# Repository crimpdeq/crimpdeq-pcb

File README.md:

# Crimpdeq PCB

PCB design for Crimpdeq in [tscircuit](https://tscircuit.com), source in
[`index.circuit.tsx`](index.circuit.tsx). See the [Crimpdeq book](https://book.crimpdeq.com/)
for assembly, flashing, and calibration.

V4 started as a tscircuit port of [v2.0.0](https://github.com/crimpdeq/crimpdeq-pcb/tree/v2.0.0)
with the HX711 replaced by a TI ADS1220 24-bit ADC, developed in
[crimpdeq-tscircuit](https://github.com/crimpdeq/crimpdeq-tscircuit) (history merged here).
The KiCad revisions V1 to V3 remain available at their release tags.

## Revisions

Use the [firmware](https://github.com/crimpdeq/crimpdeq-firmware) and
[case](https://github.com/crimpdeq/crimpdeq-case) releases in the row for your PCB revision.
From V2 on, the PCB, firmware, and case share the major version; V1 uses firmware and case
`v0.4.0`.

| PCB revision | PCB release | Source | ADC | Firmware | Case |
| --- | --- | --- | --- | --- | --- |
| V4 (in development) | not released | tscircuit | ADS1220 | not released | not released |
| V3 | [`v3.0.0`](https://github.com/crimpdeq/crimpdeq-pcb/releases/tag/v3.0.0) | KiCad | ADS1220 | [`v3.0.0`](https://github.com/crimpdeq/crimpdeq-firmware/releases/tag/v3.0.0) | [`v3.1.0`](https://github.com/crimpdeq/crimpdeq-case/releases/tag/v3.1.0) |
| V2 | [`v2.0.0`](https://github.com/crimpdeq/crimpdeq-pcb/releases/tag/v2.0.0) | KiCad | HX711 | [`v2.1.0`](https://github.com/crimpdeq/crimpdeq-firmware/releases/tag/v2.1.0) | [`v2.0.0`](https://github.com/crimpdeq/crimpdeq-case/releases/tag/v2.0.0) |
| V1 | [`v1.0.1`](https://github.com/crimpdeq/crimpdeq-pcb/releases/tag/v1.0.1) | KiCad | HX711 | [`v0.4.0`](https://github.com/crimpdeq/crimpdeq-firmware/releases/tag/v0.4.0) | [`v0.4.0`](https://github.com/crimpdeq/crimpdeq-case/releases/tag/v0.4.0) |

V3 firmware and case do not work with V4: V4 is 17 × 25.75 mm with the ESP32-C3 antenna
overhanging its edge, its wire pads differ, its load cell is powered only while
firmware sets the ADS1220 `PSW` bit (see below), and its status LED takes data on IO20
and is powered only while IO2 is low.

## Board

- Board: 17 × 25.75 mm, 4 layers, components on both sides (v2.0.0: 23 × 63.8 mm, 2 layers)
- Top: ESP32-C3-MINI-1 (its antenna overhangs the board edge: no board under it),
  USB-C (TYPE-C-31-M-12, flush with the opposite edge), USB ESD, both LEDs, load cell
  ferrites (FB1, FB2)
- Bottom: charger, power path, 3V3 buck, MAX17048, ADS1220 and passives
- Stackup: GND pour on every layer; inner2 (next to the bottom side) is a solid GND
  plane under the buck, the ADS1220 front end and the USB pair's inner1 run, and inner1
  under its top-side run (`lib/gndPlane.ts`); signals run on the other layers and the
  rest of the inner layers. GND stitching vias at the module EPAD, the ADS1220 bypass
  capacitors and AVSS, the buck, the USB pair's vias and the board edges
- Design rules (PCBWay): 5/5 mil track/space, vias 0.3 mm drill / 0.5 mm pad,
  0.3 mm copper-to-edge

## ADS1220 hookup

| ADS1220 | Net |
| --- | --- |
| AVDD, DVDD | 3V3 |
| REFP0 | load cell E+: 3V3 through 10 Ω (R22), 1 µF to GND (C14) |
| REFN0, AIN3/REFN1 | load cell E−, switched to AVSS by the internal low-side switch |
| AVSS, DGND, CLK, EP | GND |
| SCLK / DIN / DOUT/DRDY / CS | GPIO5 / GPIO4 / GPIO1 / GPIO3, CS pulled up to 3V3 (100 kΩ) |
| DRDY | GPIO0 |
| AIN0 / AIN1 | load cell S+ / S− through a GHz ferrite (FB1/FB2, at J3) and 1 kΩ each, 10 nF C0G differential (~8 kHz), 22 pF and 1 nF C0G to GND each |
| AIN2 | not connected |

The bridge is powered only while the low-side switch is closed: firmware must set
`PSW = 1` (config register 2), which closes the switch on START/SYNC and opens it on
POWERDOWN. REFP0 and REFN0 sense the bridge on both sides, so the reference stays
ratiometric across R22 and the switch.

Wire pads: J3 `E+ S+ S- E-` (E+ = filtered 3V3, E− = low-side switch), J4 `SW- SW+ B+ B-` (SW+ = B+, SW− = power-path input).
v2.0.0 names these the other way round: its `SW+` pad is the power-path input and `VBAT` is the battery.
J3's labels are on the bottom side only: FB1/FB2 sit next to its pads on the top side.

The board ends where U1's antenna starts, so the antenna overhangs the board by 5.4 mm.
Espressif recommends placing the PCB antenna outside the base board and cutting off any
board under it. U1's top pads end 0.3 mm from the edge (PCBWay's minimum). Coordinates
keep the origin of the earlier 31.5 mm board, whose top edge was at the antenna tip, so
the board center is at y = −2.875 mm. The case must hold the overhanging antenna
without touching it.

## Changes vs v2.0.0 beyond the ADC

- HX711 support parts (Q1, R5, R6, C11 VBG) removed; ADS1220 decoupling added.
- Load cell excitation switched off in power-down by the ADS1220 low-side switch
  (v2.0.0 turns the HX711 E+ regulator off instead).
- Smaller, equivalent parts: L1 FTC252012S2R2MBCA (2520, 2.2 µH, 3 A), D2/D8 B5819WS (SOD-323).
- RGB LED: XL-2121RGBC-2812B (2 × 2 mm, WS2812 protocol). Its datasheet gives
  3.0–5.5 V only as the supply limit and full function at 4.5–5.5 V, so at 3.3 V
  blue and green may be dim; the WS2812B-5050 (3.7–5.3 V) was also run at 3.3 V.
- Added: 4.7 kΩ I2C pull-ups (MAX17048), 100 nF at the RGB LED, a battery GND pad (B−).
- ADS1220 100 nF bypass capacitors (C11, C13) 0.5 mm from AVDD/DVDD, with GND vias at
  their GND pads; 3V3 reaches their pads before the pins (from the 3V3 trunk through C13).
- RGB LED supply switched by a P-MOSFET (Q3, NTK3139P), so deep sleep doesn't pay
  its idle current (V3 fed it from 3V3 whenever the battery switch was on,
  [crimpdeq-pcb#30](https://github.com/crimpdeq/crimpdeq-pcb/issues/30)): IO2 low
  powers D4, and the 100 kΩ gate pull-up (R26) keeps it off in deep sleep and reset
  and gives the IO2 strapping pin the pull-up Espressif recommends. The LED data moved
  to IO20 (RXD0, through R13). Firmware must keep the data line low while D4 is off:
  driven high, it can power D4 through the LED's input. Q3's 3V3 side doesn't run
  along the ADS1220 supply path (`scripts/drc.ts` checks this).
- USB-C shield tied directly to GND (R17 0 Ω removed).
- 3V3 buck laid out after the SY8088 layout notes, with its power copper routed by hand:
  C15's GND pad lines up with the gap between FB and IN, so a 0.8 mm strap reaches
  the GND pin under the package; C17's GND pad joins C15's; LX reaches L1 in 0.7 mm;
  the feedback divider sits at the FB pin and senses 3V3 at C17.
- 3V3 from C17 to the ESP32 decoupling (D3, C4, C2, C1, C9) is a 0.4 mm hand-routed
  trunk (v2.0.0 used up to 0.61 mm).
- ESD diode and receptacle GND pads are tied by hand to the J2 GND pins, the shell legs
  and (D7) a via.
- USB D-/D+ run as a pair (0.15 mm at 0.3 mm pitch) from the ESD diodes to IO18/IO19:
  on inner1 over a solid inner2 GND region, then through a via pair below U1 and on the
  top side over a solid inner1 region. The lengths differ by 0.3 mm; `scripts/drc.ts`
  (`usbPair`) checks that both run on the same layers within 0.5 mm. No impedance
  control is ordered: at USB full speed (12 Mbit/s) these 16 mm are electrically short.
- Download-mode recovery: bottom-side pads under U1, EN (TP1), GND (TP2) and BOOT
  (TP3, IO9), 1.5 mm apart. Hold BOOT to GND and tap EN to GND (tweezers bridge
  neighbouring pads). With the battery switch off, plugging USB in is a power-on
  reset, so holding BOOT while plugging in does the same. A 10 kΩ pull-up (R25)
  holds IO8 high, which download mode needs.
- RF filtering of the load cell inputs against BLE TX pickup
  ([crimpdeq-tscircuit#23](https://github.com/crimpdeq/crimpdeq-tscircuit/issues/23)): on the KiCad
  revision-3 board, BLE transmissions add spikes of up to 0.98 kg that enter at AIN0/AIN1.
  Each input has, between its 1 kΩ resistor and the pin, 22 pF C0G to GND (self-resonant
  near 2.4 GHz; C20, C21) and 1 nF C0G common-mode to GND (C22, C23, a tenth of C12),
  and S+/S− have GHz ferrites (BLM15HG102SN1D, FB1, FB2) at J3. Vias can't go under
  U1's left pad column, so AIN0's capacitors return to C11's GND via and AIN1's to U1's
  GND20 pad (C21, through a via) and C3's GND pad (C23). S+/S− run side by side on
  inner1, 0.35 mm apart from beside U3 down to the ferrites.
- The buck EN pull-up (R14) gets VSYS from U6.IN over inner1: on the bottom side the GND
  strap, U6 and L1 close U6.IN off from the feedback divider column.
- All copper is fixed (see Routing): hand-written traces for the buck, the 3V3 trunk,
  the USB and ESD fan-out, the charger signals, U5's I2C and alert, the ADS1220 fan-out,
  front end and supply, the load cell lines and the RGB LED corner; generated routes
  for the other nets.

## Verify

```sh
bun install --frozen-lockfile   # exact tool versions from bun.lock
npm run verify   # netlist + routing baselines, placement, schematic, build, per-check DRC,
                 # gerber shorts, fab paste and copper
npm run fab      # PCBWay package in dist/fab/
```

`scripts/drc.ts` runs every PCB check individually because the built-in DRC
aborts when its copper-pour check crashes, and adds minimum trace width, inner-layer
GND plane, 3V3 supply topology (at most 3 mm of the buck -> U1 3V3 path below
0.25 mm), USB pair and through-via checks. The board sets `isViaInPadAllowed` for C13's 3V3 via,
the only via whose drill overlaps a pad (there is no room for it between C13's pads);
`scripts/drc.ts` runs `checkViasInPads` without that flag and fails any other via in
a pad.
`scripts/netlist.py` and `scripts/routing.py` compare
connectivity and routed copper against `scripts/netlist.expected.json` and
`scripts/routing.expected.json`.

`scripts/fab-json.ts` fixes the paste and GND pours in the copy of `circuit.json`
that `npm run fab` exports, and checks the result: tscircuit leaves pill and
polygon pads without paste, shrinks all paste to 49 % of the pad area, pastes
every plated hole on both sides, and leaves floating pour copper. It also
unrotates the pads at multiples of 90° (size swapped): tscircuit flashes rounded
rotated pads with a `%LR` load rotation that some CAM tools ignore, and `npm run fab`
fails if any `%LR` is left.

Every via is a through via: the board is ordered as a standard 4-layer stackup.
tscircuit core gives vias in fixed traces (non-empty `pcbPath`) only the layers they
join, which exports blind/buried drill files with GND pour over their drill on the
other layers; `scripts/patch-core.mjs` (run on install) gives them all layers, as
core already does for autorouted vias. `scripts/drc.ts` (`throughVias`) fails on
any via that doesn't span all layers, and `npm run fab` fails on any drill file
besides `drill-PTH.drl` and `drill-NPTH.drl`.

`npm run fab` also joins each slot (J2's shell legs) onto one `X..Y..G85X..Y..`
line: the exporter puts the start hit and `G85` on separate lines, which GerbView
reads as one route through the following holes, and `npm run fab` fails if a `G85`
line is left without its start. The zip leaves out `F_Fab.gbr` and `B_Fab.gbr`
(assembly outlines, which the assembly drawings carry).

## Online viewer

<https://tscircuit.crimpdeq.com> serves the PCB, schematic and 3D viewer as a
static site on Cloudflare Pages (project `crimpdeq-tscircuit`).
`.github/workflows/site.yml` rebuilds and deploys it on every push to `main`
(repository secret `CLOUDFLARE_API_TOKEN`, Cloudflare Pages: Edit). Both the
workflow and `npm run site` refuse to publish a routing that differs from
`scripts/routing.expected.json`.

```sh
npm run site          # static site in dist/site/
npm run site:deploy   # build and upload it (needs `npx wrangler login`)
```

## PCBWay order

`dist/fab/` contains `pcbway_gerbers.zip` (Gerbers + drills), `pcbway_bom.csv`
(grouped by manufacturer part number, with LCSC codes as sourcing hints and
substitution notes), `pcbway_centroid.csv` (mm, in the Gerbers' coordinates, whose origin is
2.875 mm above the board center) and
top/bottom assembly drawings from `scripts/assembly.ts` (bottom mirrored, as seen
from below; the corner triangle marks pin 1, or the cathode of diodes and LEDs).

The silkscreen has no reference designators, which are illegible at this size and
are on the assembly drawings: its only text is the J3/J4 wire pad labels and the
EN/GND/BOOT recovery pad labels, as large as the pads and parts around them allow
and running along their pad columns. `npm run fab` widens every silkscreen line
below 0.15 mm (text is stroked at 9 % of its font size) to 0.15 mm, PCBWay's minimum. The polarized diodes (D1, D2, D8) have their
silkscreen outline closed at the cathode; D3, D7, D9 and D10 are bidirectional.

`.github/workflows/release.yml` builds the same package on every published GitHub
release, after `npm run verify` passes, and attaches it to the release as
`crimpdeq-pcb-<tag>-*` with a `SHA256SUMS` file. Pull requests that change
the fab scripts and manual runs only build it, as a workflow artifact.

Quote settings: 4 layers, 17 × 25.75 mm, 1.6 mm FR-4, min track/spacing 5/5 mil,
min hole 0.3 mm, assembly on both sides. The centroid rotations come from
tscircuit; ask PCBWay to confirm orientation against the assembly drawings.

Assembly notes for PCBWay:

- Reflow the bottom side first; the top carries the heavy parts (U1, J2).
- J2's four shell legs are pin-in-paste in the top reflow: top paste over the leg
  pads, none on the bottom.
- The J3/J4 wire pads have no paste; the load cell and battery wires are
  hand-soldered afterwards.
- Paste is 1:1 on normal pads and 50–60 % on the thermal pads (U1 EPAD, U3 and
  U5 exposed pads).

## Routing

All copper is fixed; the autorouter has nothing left to route.

- GND is left to the GND pours on all four layers and the stitching vias.
  `lib/gndPlaneRouter.ts` removes it from the autorouter input, and
  `checkEachPcbPortConnectedToPcbTraces` fails if any GND pad ends up on its own
  copper island (a pad boxed in by other traces needs a via or a trace of its own,
  as C14's and U1.GND4's do).
- Traces with a layout intent are written by hand in `index.circuit.tsx` (see the
  design changes above).
- The other nets (VSYS, VBUS, VBAT, the rest of 3V3, the SPI clock and data, CS,
  the LED supply, switch gate and data, CHIP_PU, BOOT) are generated into
  `lib/handRoutes.ts` by `scripts/handroute.sh`. It builds the board without them
  and without the autorouter (`GND_ROUTER_SKIP=1`), then `scripts/handroute.ts`
  routes the nets in `scripts/handroute.json`, in that order, on a 0.05 mm grid over
  the four layers:
  0.127 mm to other nets, vias 0.15 mm from pads, through vias that block every
  layer, and the GND plane regions kept clear.

After a change to placement, footprints or the hand-written traces:

```sh
scripts/handroute.sh             # regenerates lib/handRoutes.ts
npm run verify                   # fails on the routing baseline: expected
python3 scripts/routing.py --update && npm run verify
```

If a net doesn't route, `scripts/handroute.sh` fails and leaves `lib/handRoutes.ts`
unchanged: move it earlier in `scripts/handroute.json` (earlier nets get the room) or
change the hand-written traces around it.

Hand-written traces are `<trace>` elements with a non-empty `pcbPath`
(`pcbPath={[toPort]}` for a straight line between pad centers): core fixes only
those, and the autorouter routed across `pcbPath={[]}` ones. `pcbStraightLine` ends
traces at the pad edge, and tscircuit then attaches the end to whichever pad covers
that point on any layer (here U1's pads on the top side). Core limits traces to a
power-to-ground capacitor to 1 mm and skips autorouting (and fails the build) if a
fixed trace is longer; capacitors with longer fixed traces set
`maxDecouplingTraceLength`.

The tscircuit autorouter is deterministic, but at this density it left via-to-pad
violations and shorts that its own DRC misses, routed across fixed traces, and placed
vias it checked on only some of the layers they cross. `scripts/search.py` (nudges
passives until the board routes clean) and its output depending on the platform
(macOS arm64 against Linux x64) only matter again if nets are left to it.
`lib/gndPlaneRouter.ts` keeps it in place: the stock solver with GND removed and the
`unbroken` inner-layer GND pours detached from GND, so they only keep other nets out.
Attached, the router escaped nearby GND pads into the pour with vias whose clearance
it checked only between the pad and pour layers; built as through vias, they landed
on pads on the other side (L1, C16, C17, C11, C12). Routing on only three layers (all
of inner2 reserved) left the board unroutable.

## Prompting AI agents

Agents follow `AGENTS.md` and the vendored tscircuit skill. tscircuit's
[prompting guide](https://docs.tscircuit.com/guides/circuit-generation/generating-circuit-boards-with-ai)
is written for new boards; a prompt for a change to this one should state:

- Goal: the change and why.
- Scope: the parts, nets or board area, by reference designator or net name.
- Parts: the manufacturer part number of new or changed parts.
- Side effects: whether placement, routed copper or connectivity may change, and whether
  to regenerate `dist/fab/`.
- Done: `npm run verify` passes, plus anything to inspect (PCB image, DRC result).

```text
<Change> because <reason>.
Affected: <reference designators, nets or board area>.
New parts: <manufacturer part number> (LCSC <code> as a sourcing hint).
May change: <placement | hand-written traces | generated routes | netlist | dist/fab/>.
Keep fixed: <parts or traces that must not move or reroute>.
Done when npm run verify passes; show the netlist and routing diffs before
updating their baselines.
```

The PCB was sponsored by [PCBWay](https://www.pcbway.com/), thank you! Working with them was incredibly easy and fast, and the resulting boards are high quality.

## License

This repository is source-available for personal and educational use only.

Commercial manufacture, sale of PCBs, sale of 3D-printed cases, kits, or assembled Crimpdeq devices requires prior written permission.

The vendored tscircuit skill in `.agents/skills/tscircuit/` keeps its own MIT license.

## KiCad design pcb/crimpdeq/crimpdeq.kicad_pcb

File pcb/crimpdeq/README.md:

# Crimpdeq — 30 x 30 mm Four-Layer Design

This is the repository's single canonical PCB design, released as PCB V3 in `v3.0.0`. It
includes corrected ESP32 module grounding, an ADS1220 load-cell front-end, and compact
power/USB routing.

- Board/project/rules/schematic: `crimpdeq.{kicad_pcb,kicad_pro,kicad_dru,kicad_sch}`
- Outline: 30.00 x 30.00 mm (30.05 x 30.05 mm including edge stroke)
- Components: 59 total, 38 front / 21 back
- U1 antenna and D4 LED: back; J2 USB-C and U3 ADS1220: front
- U1 pins 37–53, including EPAD 49, are connected to GND as required by Espressif.
- R20/R21/R22 provide 10 kΩ pull-ups for SDA, SCL, and the MAX17048 alert output.
- U3 ADS1220 (TSSOP-16, LCSC C48263) uses ratiometric +3V3 excitation (E+/REFP0) with
  E-/REFN0 on GND. AVDD/DVDD decoupling is C11 + C19. R7/R8 and 100 nF C0G C12 filter into AIN0/AIN1.
- SPI map: GPIO5 SCK, GPIO4 MOSI, GPIO3 CS, GPIO1 MISO (DOUT/~DRDY). R23–R26 are
  source-local 47 Ω series dampers on those four signals. CLK is grounded and dedicated DRDY is NC.
- The buck input, switch, output, and feedback components form a compact front-side cluster.
- Twelve dedicated GND stitching vias tie the outer floods to the solid L2 plane.
- All four load-cell pads (`E-`, `A-`, `A+`, `E+`) are together on the bottom edge near U3 and
  away from the antenna. `B-`, `B+`, `SW+`, and `SW-` are on the right edge, next to the USB-C
  connector.
- The ESP32 antenna body overhangs the top edge; its all-layer copper keepout is retained.
- The USB-C housing overhangs the bottom edge by 1.00 mm; connector copper remains in-board.
- L2 is a signal-free GND plane. L3 carries the 3V3 pour and low-speed signals.
- KiCad error-level DRC: zero violations and zero unconnected items.
- Schematic ERC and PCB/schematic parity: zero errors.

Production files:

- Gerbers, drills, BOM, and pick-and-place files: GitHub Release artifacts
- Assembly source and generators: `assembly/`

Check the manufacturer's DFM review on every order.

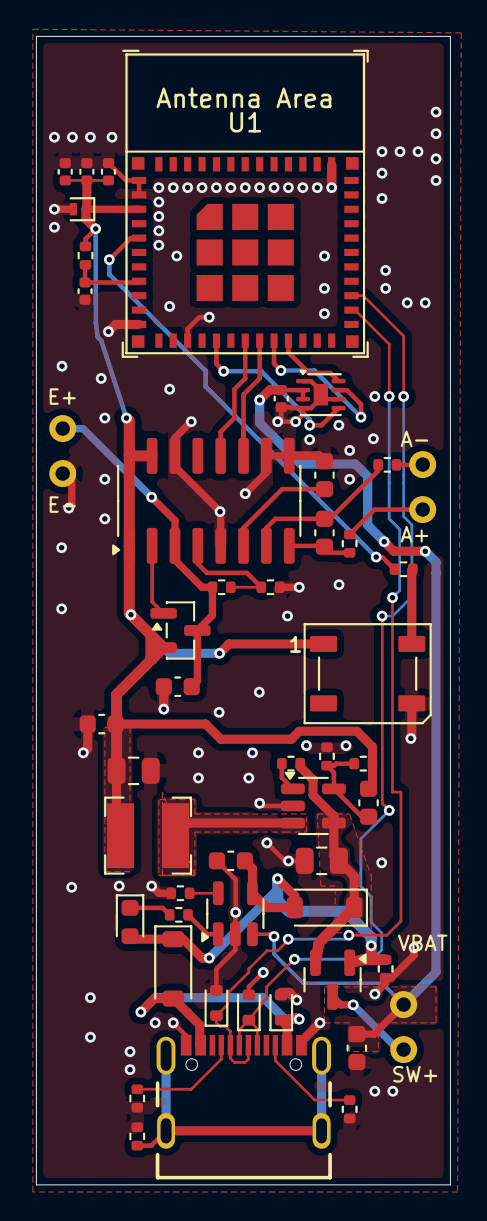
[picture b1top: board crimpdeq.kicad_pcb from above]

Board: 2 copper layers, 23.0 x 63.8 mm, 48 parts (0 on the bottom side), 34 nets.

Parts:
C1, C3: 1uF 16V; C_0402_1005Metric
C2, C18: 100nF 10V; C_0402_1005Metric
C4: 10nF 10V; C_0402_1005Metric
C5, C6: 4.7uF 16V; C_0603_1608Metric
C9, C10: 10uF; C_0603_1608Metric
C11, C12: 0.1uF; C_0603_1608Metric
C15, C17: 10uF 16V; C_0805_2012Metric
C16: 22pF 50V; C_0603_1608Metric
D1: LED; LED_0603_1608Metric
D2, D8: B5819W; D_SOD-123
D3: LESD8D3.3CAT5G; D_SOD-882
D4: WS2812B; LED_WS2812B_PLCC4_5.0x5.0mm_P3.2mm
D7, D9, D10: LESD5D5.0CT1G; D_SOD-523
J2: USB4105-GF-A; GCT_USB4105-GF-A
J3: Loadcell_Pads; External_Cable_Pads_Left
J4: Power_Sense_Pads; External_Cable_Pads_Right
L1: SPH4018H2R2MT (2.2uH 2.2A); L_Bourns-SRN4018
Q1: SS8550; SOT-23
Q2: DMG3415U; SOT-23
R1, R2, R14: 10kR 1%; R_0402_1005Metric
R3: 1kR 1%; R_0402_1005Metric
R5: 12kR 1%; R_0402_1005Metric
R6: 8k2R 1%; R_0402_1005Metric
R7, R8: 100R 1%; R_0402_1005Metric
R9, R15: 100kR 1%; R_0402_1005Metric
R13, R17: 0R 1%; R_0402_1005Metric
R16: 22k1R 1%; R_0402_1005Metric
R18, R19: 5k1R 1%; R_0402_1005Metric
U1: ESP32-C3-MINI-1
U2: MCP73831T-2ACI/OT; SOT-23-5
U3: HX711; SOP-16_3.9x9.9mm_P1.27mm
U5: MAX17048G+T10; TDFN-8-1EP_2x2mm_P0.5mm_EP0.8x1.2mm
U6: SY8088; SOT-23-5

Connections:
+3V3: C1.1, C2.1, C4.1, C9.1, C16.1, C17.1, D3.1 (A1), D4.1 (VDD), L1.2, Q1.2 (E), R1.1, R15.1, U1.3 (3V3), U3.1 (VSUP), U3.15 (RATE), U3.16 (DVDD)
+BATT: C6.1, C18.1, J4.3 (VBAT), U2.3 (VBAT), U5.2 (CELL), U5.3 (VDD)
/Buck_Coil: L1.1, U6.3 (LX)
A+: J4.2 (A+), R7.2
A-: J4.1 (A-), R8.2
CHIP_PU: C3.1, R1.2, U1.8 (EN/CHIP_PU)
E+: C10.1, J3.1 (E+), Q1.3 (C), R5.1, U3.3 (AVDD)
ENABLE: R14.2, U6.1 (EN)
GND: C1.2, C2.2, C3.2, C4.2, C5.1, C6.2, C9.2, C10.2, C11.1, C15.2, C17.2, C18.2, D3.2 (A2), D4.3 (VSS), D7.2 (A2), D9.2 (A2), D10.2 (A2), J2.A1_B12 (GND), J2.B1_A12 (GND), J3.2 (E-), R2.1, R6.2, R9.2, R16.2, R17.2, R18.2, R19.2, U1.1 (GND), U1.2 (GND), U1.11 (GND), U1.14 (GND), U1.36 (GND), U2.2 (VSS), U3.5 (AGND), U3.9 (INB-), U3.10 (INB+), U3.14 (XI), U5.1 (GND), U5.4 (GND), U5.6 (QSTRT), U5.9 (GND), U6.2 (GND)
IO2_LED: R13.1, U1.5 (GPIO2/ADC1_CH2)
IO4_DATA: U1.18 (GPIO4/ADC1_CH4), U3.12 (DOUT)
IO5_SCK: U1.19 (GPIO5/ADC2_CH0), U3.11 (PD_SCK)
IO6_SDA: U1.20 (GPIO6), U5.7 (SDA)
IO7_SCL: U1.21 (GPIO7), U5.8 (SCL)
IO10_ALRT: U1.16 (GPIO10), U5.5 (~ALRT)
unnamed: D1.1 (K), R3.2
unnamed: D4.4 (DIN), R13.2
unnamed: D8.2 (A), D9.1 (A1), J2.A4_B9 (VBUS), J2.B4_A9 (VBUS)
unnamed: J2.A5 (CC1), R19.1
unnamed: J2.B5 (CC2), R18.1
unnamed: J2.S1 (SHELL_GND), J2.S2 (SHELL_GND), J2.S3 (SHELL_GND), J2.S4 (SHELL_GND), R17.1
unnamed: Q1.1 (B), U3.2 (BASE)
unnamed: R2.2, U2.5 (PROG)
unnamed: R3.1, U2.1 (STAT)
unnamed: C12.1, R7.1, U3.8 (INA+)
unnamed: C12.2, R8.1, U3.7 (INA-)
unnamed: C11.2, U3.6 (VBG)
unnamed: R5.2, R6.1, U3.4 (VFB)
unnamed: C16.2, R15.2, R16.1, U6.5 (FB)
SW_BATT: J4.4 (SW+), Q2.3 (D)
USB_D+: D10.1 (A1), J2.A6 (DP1), J2.B6 (DP2), U1.27 (GPIO19/USB_D+)
USB_D-: D7.1 (A1), J2.A7 (DN1), J2.B7 (DN2), U1.26 (GPIO18/USB_D-)
VBUS: C5.2, D1.2 (A), D2.2 (A), D8.1 (K), Q2.1 (G), R9.1, U2.4 (VDD)
VSYS: C15.1, D2.1 (K), Q2.2 (S), R14.1, U6.4 (IN)

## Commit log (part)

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2026-02-17 docs: Add PCB results
2026-02-18 feat: Rename hardware folder to pcb
2026-02-18 feat: Initial 3D models
2026-02-18 feat: Add switch and rails to avoid components moving
2026-02-18 feat: Add "crimpdeq" and show_lid variable
2026-02-18 feat: Add CAD ci
2026-02-18 feat: Round corners
2026-02-18 feat: Improvements and cleanups
2026-02-19 feat: Add LED and better fixations for pcb
2026-02-19 feat: Update switch to KD1
2026-02-19 feat: Use only 2 notches and short guide for the loadcell
2026-02-20 feat: Use KCD11 instead of KCD1 and add a dimensions file to reduce duplication
2026-02-20 ci: Add GHA workflows
2026-02-20 feat: Make LED hole bigger, update battery thickness, remove duplication of dimensions
2026-02-20 feat: Make usb-c hole a bit bigger
2026-02-20 feat: Merge the screw colums into the enclosure walls
2026-02-20 fix: Lid holes
2026-02-20 feat: Make the lid close the huge gaps, round the usb connector
2026-02-23 feat: Add supports and constrains on the main part, simplify the lid. Now the loadcell has supports to avoid the glue on the middle of it
2026-02-23 feat: Make printing simplifications
2026-02-23 feat: Emebed the LED on the pcb, reduce the gap between the lid and the pcb
2026-02-23 fix: Fix loadcell assamblage
2026-02-23 feat: Avoid collisions
2026-02-23 feat: Add collision check
2026-02-23 fix: Typo
2026-02-23 feat: Update clearance
2026-02-23 feat: Update horizontal constrains of the battery
2026-02-23 feat: Avoid hanging supports of the battery
2026-02-23 feat: Update rear PCB stoppers to serve as horzintal constrain for the battery
2026-02-23 feat: Add vertical constrain for PCB
2026-02-24 feat: Add a small cube to hold the battery horizontal
2026-02-25 feat: Remove 3D case files
2026-02-25 Add GHA checks (#6)
    * feat: Rename hardware folder to pcb
    * feat: Initial 3D models
    * feat: Add switch and rails to avoid components moving
    * feat: Add "crimpdeq" and show_lid variable
    * feat: Add CAD ci
    * feat: Round corners
2026-02-25 docs: Update links
2026-03-12 fix: add assembly notes for manufacturing
2026-03-12 ci: Ignore lib_footprint issues/mismatches
2026-03-12 fix: resolve KiCad ERC and DRC failures
2026-03-12 ci: fail KiCad checks only on error-level violations
2026-03-12 Ignore lib_footprint issues/mismatches (#10)
    * ci: Ignore lib_footprint issues/mismatches
    * fix: resolve KiCad ERC and DRC failures
    * ci: fail KiCad checks only on error-level violations
2026-03-12 ci: Add adinitonal notes on bom
2026-04-09 ci: format release bom with assembly notes
2026-04-10 fix: switch Q1 to SOT-23 SS8550
2026-04-10 revert: switch Q1 to SOT-23 SS8550
2026-04-10 fix: add Q1 copper keepout for KiCad 9 CI
2026-04-11 fix: switch Q1 to SOT-23 SS8550 (#13)
    * fix: switch Q1 to SOT-23 SS8550
    * fix: add Q1 copper keepout for KiCad 9 CI
2026-04-12 fix: trim U4 pads and reroute board
2026-04-12 fix: use KiCad 10 in workflows
2026-04-12 fix: use published KiCad 10 action tag
2026-04-13 fix: align release bom generation with local output
2026-04-13 chore: Update gitingore
2026-04-13 Tim U4 pads and reroute board (#14)
    * fix: trim U4 pads and reroute board
    * fix: use KiCad 10 in workflows
    * fix: use published KiCad 10 action tag
2026-04-14 fix: remove unused rtc crystal option
2026-04-14 fix: allow battery charging while powered off
2026-04-14 ci: add fab-friendly gerber release archive
2026-04-14 refactor: clarify system power rail naming
2026-04-14 refactor: tighten usb protection breakout routing
2026-04-14 fix: adjust Q2 and C6 placement
2026-04-14 fix: remove unused rust board pads
2026-05-12 feat: Add rbg led and route it
2026-05-12 fix: resolve schematic and layout rule violations
2026-05-12 fix: allow charging while switched off
2026-06-03 feat: Add battery gauge, review schematic/pcb
2026-06-03 fix: Via diameters
2026-06-03 feat: Fix unused tracks and cleearance violations
2026-06-03 feat: Ignore analysis folder
2026-06-03 docs: Add datasheets
2026-06-03 feat: Simplify A+/A- routing
2026-06-03 fix: DRC unconected GND
2026-06-03 fix: Remove unused tracks
2026-06-03 feat: Update Assembly note of R13
2026-06-18 chore: Update license
2026-06-30 Revision 2 (#15)
    * Tim U4 pads and reroute board (#14)
    * fix: trim U4 pads and reroute board
    * fix: use KiCad 10 in workflows
    * fix: use published KiCad 10 action tag
    * fix: remove unused rtc crystal option
    * fix: allow battery charging while powered off
2026-06-30 fix: allow USB-C connector manufacturing clearances
2026-06-30 fix: allow USB-C connector manufacturing clearances (#17)
